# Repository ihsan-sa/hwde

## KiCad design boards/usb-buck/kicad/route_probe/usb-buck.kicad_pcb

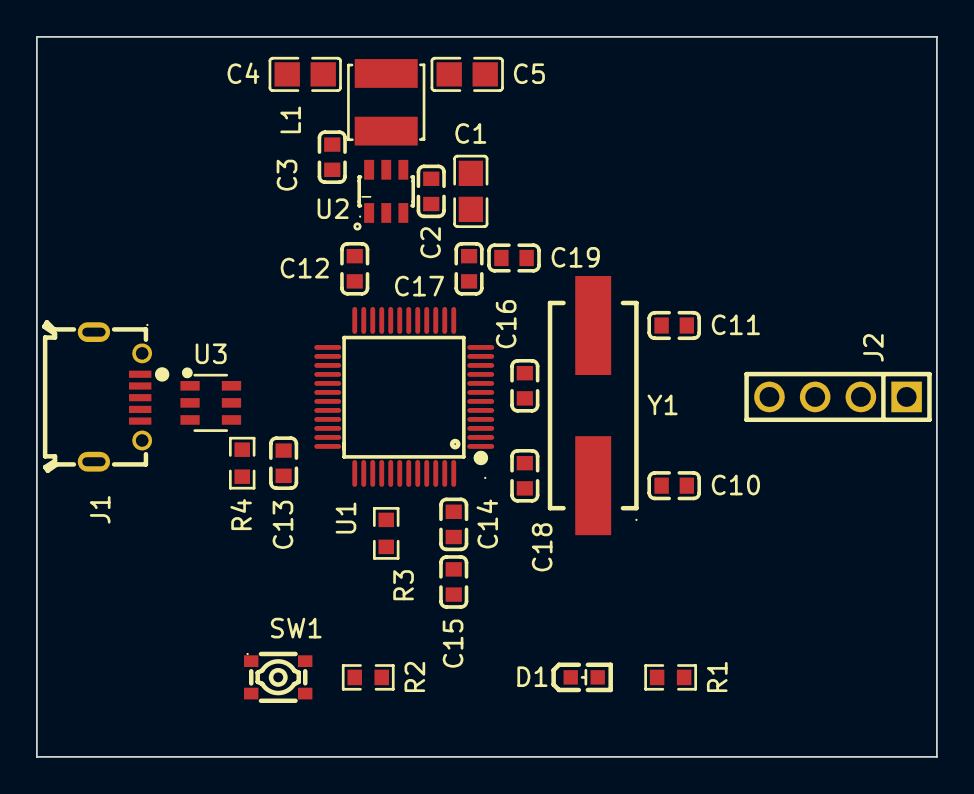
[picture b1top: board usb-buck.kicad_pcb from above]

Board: 4 copper layers, 50.0 x 40.0 mm, 28 parts (0 on the bottom side), 16 nets, no tracks yet.

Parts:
C1: 10uF 25V X5R; C0805
C2, C3, C12, C13, C14, C16, C18, C19: 100nF 50V X7R; C0603
C4, C5: 22uF 25V X5R; C0805
C10, C11: 22pF 50V C0G; C0603
C15: 4.7uF 16V X5R; C0603
C17: 1uF 50V X5R; C0603
D1: Red 0603; LED-SMD_L1.6-W0.8-R-RD
J1: USB Micro-B receptacle SMD; USB-SMD_USB-111FD-B-SU
J2: 1x4 2.54mm male THT; HDR-TH_4P-P2.54-V-M
L1: 4.7uH; IND-SMD_L4.0-W4.0
R1: 1k; R0603
R2, R3: 10k; R0603
R4: 1.5k; R0603
SW1: SMD tactile switch; SW-SMD_4P-L3.0-W2.6-P1.80-LS3.4-TL
U1: STM32F103C8T6; LQFP-48_L7.0-W7.0-P0.50-LS9.0-BL
U2: AP63203QWU-7; TSOT-26_L2.9-W1.6-P0.95-LS2.8-BL
U3: USBLC6-2SC6; SOT-23-6_L2.9-W1.6-P0.95-LS2.8-BL
Y1: 8MHz 20pF; CRYSTAL-SMD_L11.5-W4.8-LS12.7

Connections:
+3V3: C4.1, C5.1, C12.1, C13.1, C14.1, C15.1, C16.1, C17.1, C18.1, J2.1, L1.2, R1.2, R2.2, R4.2, U1.1, U1.9, U1.24, U1.36, U1.48, U2.1
/USB_DM: J1.2, U1.32, U3.1, U3.6
/USB_DP: J1.3, R4.1, U1.33, U3.3, U3.4
/mcu/BOOT0: R3.1, U1.44
/mcu/BTN: R2.1, SW1.1, SW1.2, U1.18
/mcu/LED: D1.2, U1.2
/mcu/LED_A: D1.1, R1.1
/mcu/NRST: C19.1, U1.7
/mcu/OSC_IN: C10.1, U1.5, Y1.1
/mcu/OSC_OUT: C11.1, U1.6, Y1.2
/mcu/SWCLK: J2.2, U1.37
/mcu/SWDIO: J2.4, U1.34
/power/BST: C3.1, U2.6
/power/SW: C3.2, L1.1, U2.5
GND: C1.2, C2.2, C4.2, C5.2, C10.2, C11.2, C12.2, C13.2, C14.2, C15.2, C16.2, C17.2, C18.2, C19.2, J1.5, J1.6, J1.7, J1.8, J1.9, J2.3, R3.2, SW1.3, SW1.4, U1.8, U1.23, U1.35, U1.47, U2.4, U3.2
VBUS: C1.1, C2.1, J1.1, U2.2, U2.3, U3.5

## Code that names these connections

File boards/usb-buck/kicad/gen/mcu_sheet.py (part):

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Refdes range 200s (architecture/sheets.md s2); pwr_base 200.
Exposes USB_DP / USB_DM to the root (-> /USB_DP, /USB_DM); everything else
stays sheet-internal (-> /mcu/OSC_IN, /mcu/OSC_OUT, /mcu/NRST, /mcu/BOOT0,
/mcu/SWDIO, /mcu/SWCLK, /mcu/LED, /mcu/LED_A, /mcu/BTN). constraints.json
names /mcu/OSC_IN and /mcu/OSC_OUT, so the sheet name "mcu" is contractual.
+3V3 and GND are power SYMBOLS -> global and bare, no sheet pins.

Every pin number below is re-confirmed against parts/C8734.json (ST DS5319
Rev 18), not memory: PB0 = 18, PA11 = 32, PA12 = 33, PA13 = 34, PA14 = 37,
BOOT0 = 44, VDD 24/36/48, VSS 23/35/47, VDDA 9, VSSA 8, VBAT 1, NRST 7,
OSC_IN 5, OSC_OUT 6, PC13 2.
"""
from __future__ import annotations

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                       # (ASSUMED; DS5319 2.3.9 permits it, run (a) precedent)
    "2": "LED",        # PC13 sinks D1 (3 mA backup-domain limit -> R1 1k)
    "3": "NC", "4": "NC",
    "5": "OSC_IN",     # PD0-OSC_IN, HSE
    "6": "OSC_OUT",    # PD1-OSC_OUT
    "7": "NRST",
    "8": "GND",        # VSSA
    "9": "+3V3",       # VDDA
    "10": "NC", "11": "NC", "12": "NC", "13": "NC", "14": "NC",
    "15": "NC", "16": "NC", "17": "NC",
    "18": "BTN",       # PB0 - user button, active low
    "19": "NC", "20": "NC", "21": "NC", "22": "NC",
    "23": "GND",       # VSS_1
    "24": "+3V3",      # VDD_1
    "25": "NC", "26": "NC", "27": "NC", "28": "NC", "29": "NC",
    "30": "NC", "31": "NC",
    "32": "USB_DM",    # PA11 / USBDM - no series resistors (the F103 PHY's
    "33": "USB_DP",    # PA12 / USBDP    output impedance is internal)
    "34": "SWDIO",     # PA13 / JTMS-SWDIO (reset default)
    "35": "GND",       # VSS_2
    "36": "+3V3",      # VDD_2
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        "U1", "aiee:STM32F103C8T6", "STM32F103C8T6",
        at=(215.90, 127.00), pins=U1_PINS,
        footprint=f"{FP}:LQFP-48_L7.0-W7.0-P0.50-LS9.0-BL",
        expect={"1": "VBAT", "2": "PC13", "5": "OSC_IN", "6": "OSC_OUT",
                "7": "NRST", "8": "VSSA", "9": "VDDA", "18": "PB0",
                "20": "PB2", "23": "VSS_1", "24": "VDD_1", "32": "PA11",
                "33": "PA12", "34": "PA13", "35": "VSS_2", "36": "VDD_2",
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    sh.add_component("aiee:X49SM8MSD2SC", "Y1", "8MHz 20pF", at=(76.20, 76.20),
                     footprint=f"{FP}:CRYSTAL-SMD_L11.5-W4.8-LS12.7",
                     expect={"1": "OSC1", "2": "OSC2"})
    sh.wire_pins("Y1", {"1": "OSC_IN", "2": "OSC_OUT"})
    sh.add_component("aiee:CL10C220JB8NNNC", "C10", V_22P, at=(76.20, 96.52),
                     footprint=f"{FP}:C0603")
    sh.wire_pins("C10", {"1": "OSC_IN", "2": "GND"})
    sh.add_component("aiee:CL10C220JB8NNNC", "C11", V_22P, at=(76.20, 109.22),
                     footprint=f"{FP}:C0603")
    sh.wire_pins("C11", {"1": "OSC_OUT", "2": "GND"})

    # ---- NRST protection cap (DS5319 Figure 31) ---------------------------
    sh.add_component("aiee:CC0603KRX7R9BB104", "C19", V_100N,
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    # ---- user button: SW1 to GND + R2 10k pull-up (decisions.md item 11) --
    sh.add_component("aiee:0603WAF1002T5E", "R2", "10k", at=(76.20, 152.40),
                     footprint=f"{FP}:R0603")
    sh.wire_pins("R2", {"1": "BTN", "2": "+3V3"})
    # 4-pad tactile switch: the symbol draws pins 1+2 on one internal bar and
    # 3+4 on the other, so each PAIR is one terminal - wire both pads of each
    # pair or a pad floats (ERC) and one solder joint carries the contact.
    sh.add_component("aiee:TS263065A340GFSXBDSMDTACTILESWITCH", "SW1",
                     "SMD tactile switch", at=(76.20, 177.80),
                     footprint=f"{FP}:SW-SMD_4P-L3.0-W2.6-P1.80-LS3.4-TL")
    sh.wire_pins("SW1", {"1": "BTN", "2": "BTN", "3": "GND", "4": "GND"})

    # ---- status LED: +3V3 -> R1 1k -> LED_A -> D1 -> LED -> PC13 sink -----
    sh.add_component("aiee:KT-0603R", "D1", "Red 0603", at=(76.20, 203.20),
                     footprint=f"{FP}:LED-SMD_L1.6-W0.8-R-RD",
                     expect={"1": "A", "2": "K"})
    sh.wire_pins("D1", {"1": "LED_A", "2": "LED"})
    sh.add_component("aiee:0603WAF1001T5E", "R1", "1k", at=(114.30, 203.20),
                     footprint=f"{FP}:R0603")
    sh.wire_pins("R1", {"1": "LED_A", "2": "+3V3"})

    # ---- USB D+ pull-up: MANDATORY, hard-wired (decisions.md item 3) ------
    # 1.5 k 1% to +3V3; the F103 has no internal USB pull-up and the 10 k many
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    # way) and the pull-up belongs on the MCU side of the ESD array.
    sh.add_component("aiee:0603WAF1501T5E", "R4", "1.5k", at=(76.20, 215.90),
                     footprint=f"{FP}:R0603")
    sh.wire_pins("R4", {"1": "USB_DP", "2": "+3V3"})

    # ---- SWD header J2: 1 +3V3, 2 SWCLK, 3 GND, 4 SWDIO -------------------
    # ST Nucleo CN4 debug-row order minus NRST/SWO (decisions.md item 12 /
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    sh.power_flag("GND", at=(304.80, 228.60), sym="power:GND", flag=False)

    # ---- cross-sheet pair --------------------------------------------------
    sh.hier_pin("USB_DP", shape="bidirectional", at=(304.80, 165.10))
    sh.hier_pin("USB_DM", shape="bidirectional", at=(304.80, 177.80))

    for ref, code in LCSC.items():
        sh.sch.components.get(ref).set_property("LCSC", code)
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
